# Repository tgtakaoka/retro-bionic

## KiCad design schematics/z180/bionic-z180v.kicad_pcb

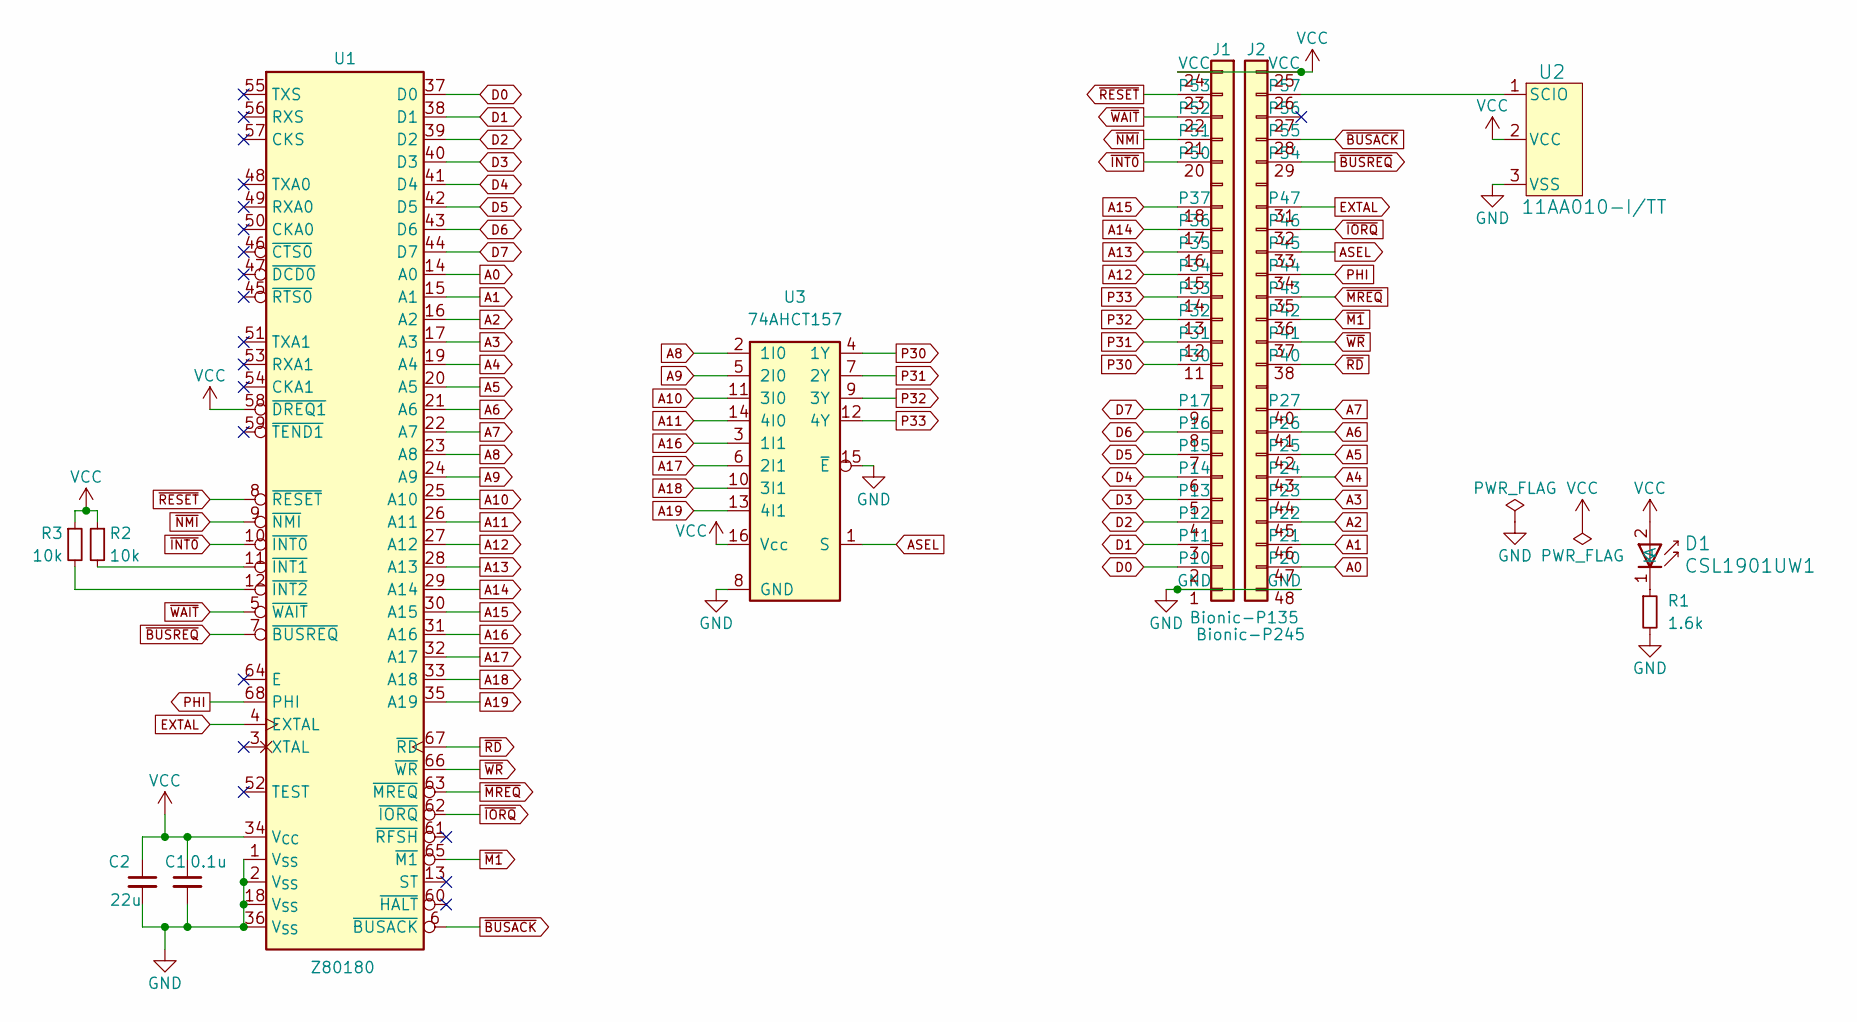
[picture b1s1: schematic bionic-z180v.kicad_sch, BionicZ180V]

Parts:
C1: 0.1u; C_0603_1608Metric_Pad1.08x0.95mm_HandSolder
C2: 22u; C_0603_1608Metric_Pad1.08x0.95mm_HandSolder
D1: CSL1901UW1; LED_CSL1901UW1_ROM-M
J1: Bionic-P135; Bionic-P135_SMT
J2: Bionic-P245; Bionic-P245_SMT
R1: 1.6k; R_0603_1608Metric_Pad0.98x0.95mm_HandSolder
R2, R3: 10k; R_0603_1608Metric_Pad0.98x0.95mm_HandSolder
U1: Z80180; 846821B1RKTP
U2: 11AA010-I/TT; SOT-23_MC_MCH-M
U3: 74AHCT157; PW16-M

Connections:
A0: J2.47 (P20), U1.14 (A0)
A1: J2.46 (P21), U1.15 (A1)
A2: J2.45 (P22), U1.16 (A2)
A3: J2.44 (P23), U1.17 (A3)
A4: J2.43 (P24), U1.19 (A4)
A5: J2.42 (P25), U1.20 (A5)
A6: J2.41 (P26), U1.21 (A6)
A7: J2.40 (P27), U1.22 (A7)
A8: U1.23 (A8), U3.2 (1I0)
A9: U1.24 (A9), U3.5 (2I0)
A10: U1.25 (A10), U3.11 (3I0)
A11: U1.26 (A11), U3.14 (4I0)
A12: J1.15 (P34), U1.27 (A12)
A13: J1.16 (P35), U1.28 (A13)
A14: J1.17 (P36), U1.29 (A14)
A15: J1.18 (P37), U1.30 (A15)
A16: U1.31 (A16), U3.3 (1I1)
A17: U1.32 (A17), U3.6 (2I1)
A18: U1.33 (A18), U3.10 (3I1)
A19: U1.35 (A19), U3.13 (4I1)
ASEL: J2.33 (P45), U3.1 (S)
D0: J1.2 (P10), U1.37 (D0)
D1: J1.3 (P11), U1.38 (D1)
D2: J1.4 (P12), U1.39 (D2)
D3: J1.5 (P13), U1.40 (D3)
D4: J1.6 (P14), U1.41 (D4)
D5: J1.7 (P15), U1.42 (D5)
D6: J1.8 (P16), U1.43 (D6)
D7: J1.9 (P17), U1.44 (D7)
EXTAL: J2.31 (P47), U1.4 (EXTAL)
GND: C1.2, C2.2, J1.1 (GND), J2.48 (GND), R1.2, U1.1 (V_{SS}), U1.2 (V_{SS}), U1.18 (V_{SS}), U1.36 (V_{SS}), U2.3 (VSS), U3.8 (GND), U3.15 (~E)
unnamed: D1.1 (K), R1.1
unnamed: J2.26 (P57), U2.1 (SCIO)
unnamed: R2.2, U1.11 (~INT1)
unnamed: R3.2, U1.12 (~INT2)
P30: J1.11 (P30), U3.4 (1Y)
P31: J1.12 (P31), U3.7 (2Y)
P32: J1.13 (P32), U3.9 (3Y)
P33: J1.14 (P33), U3.12 (4Y)
PHI: J2.34 (P44), U1.68 (PHI)
VCC: C1.1, C2.1, D1.2 (A), J1.24 (VCC), J2.25 (VCC), R2.1, R3.1, U1.34 (V_{CC}), U1.58 (~DREQ1), U2.2 (VCC), U3.16 (Vcc)
~BUSACK: J2.28 (P55), U1.6 (~BUSACK)
~BUSREQ: J2.29 (P54), U1.7 (~BUSREQ)
~INT0: J1.20 (P50), U1.10 (~INT0)
~IORQ: J2.32 (P46), U1.62 (~IORQ)
~M1: J2.36 (P42), U1.65 (~M1)
~MREQ: J2.35 (P43), U1.63 (~MREQ)
~NMI: J1.21 (P51), U1.9 (~NMI)
~RD: J2.38 (P40), U1.67 (~RD)
~RESET: J1.23 (P53), U1.8 (~RESET)
~WAIT: J1.22 (P52), U1.5 (~WAIT)
~WR: J2.37 (P41), U1.66 (~WR)

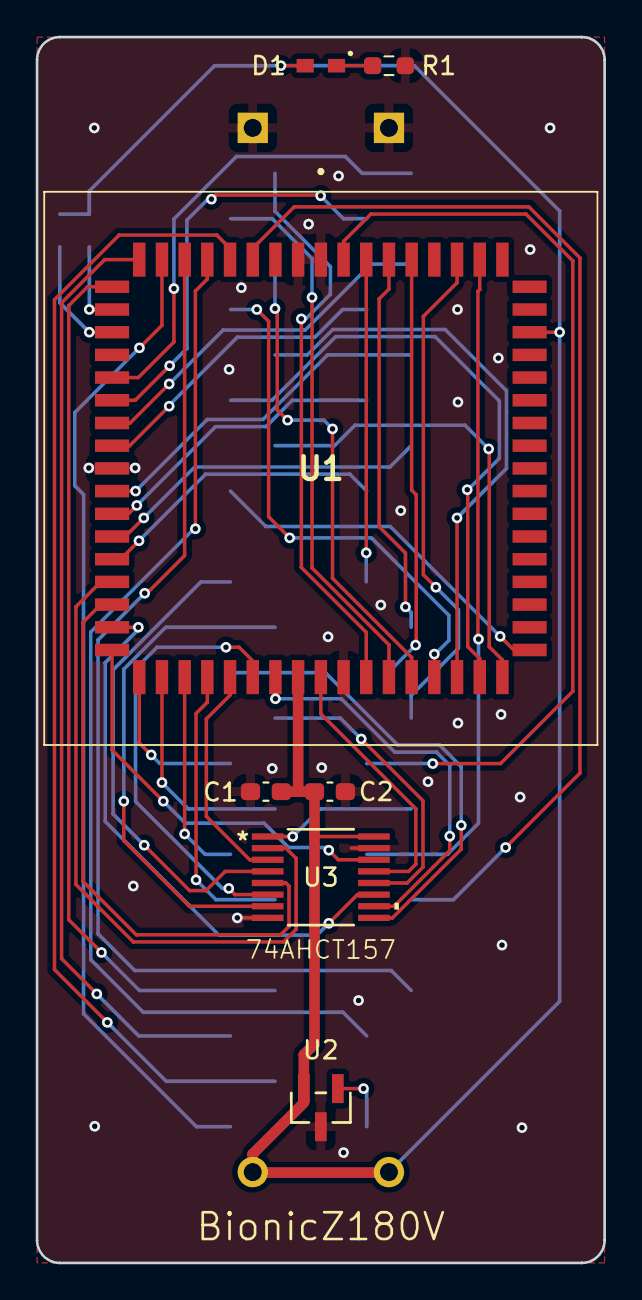
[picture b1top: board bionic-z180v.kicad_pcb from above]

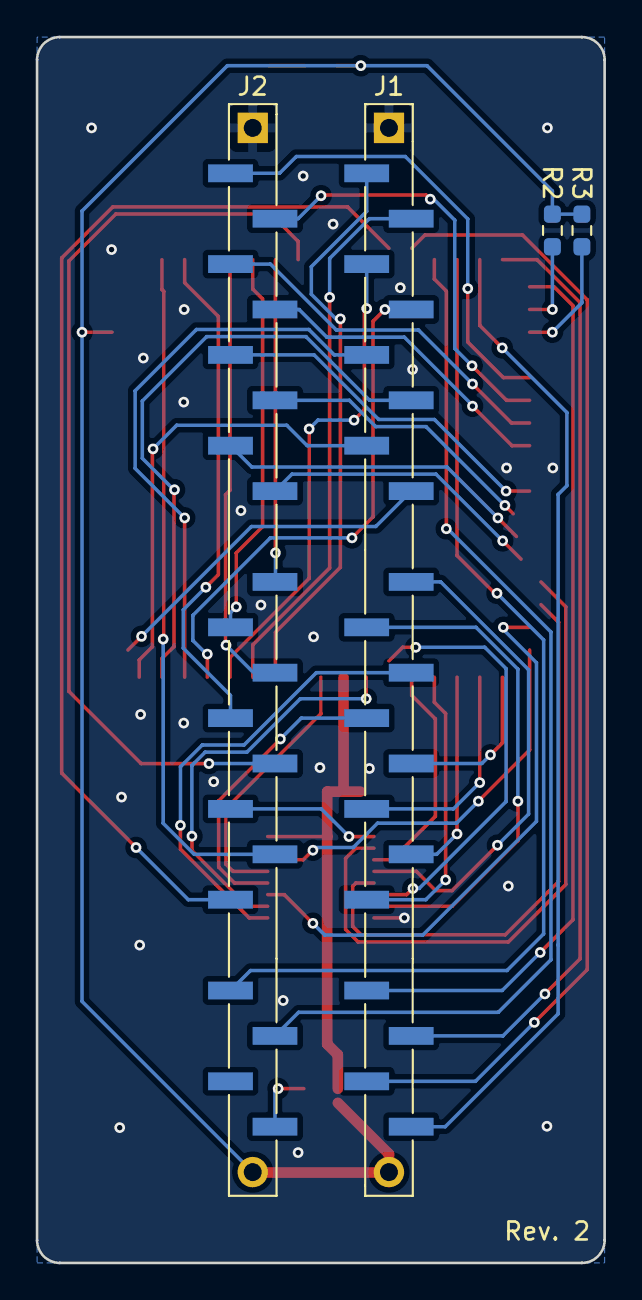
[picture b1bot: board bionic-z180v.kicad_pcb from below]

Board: 2 copper layers, 31.7 x 68.6 mm, 11 parts (4 on the bottom side), 52 nets.

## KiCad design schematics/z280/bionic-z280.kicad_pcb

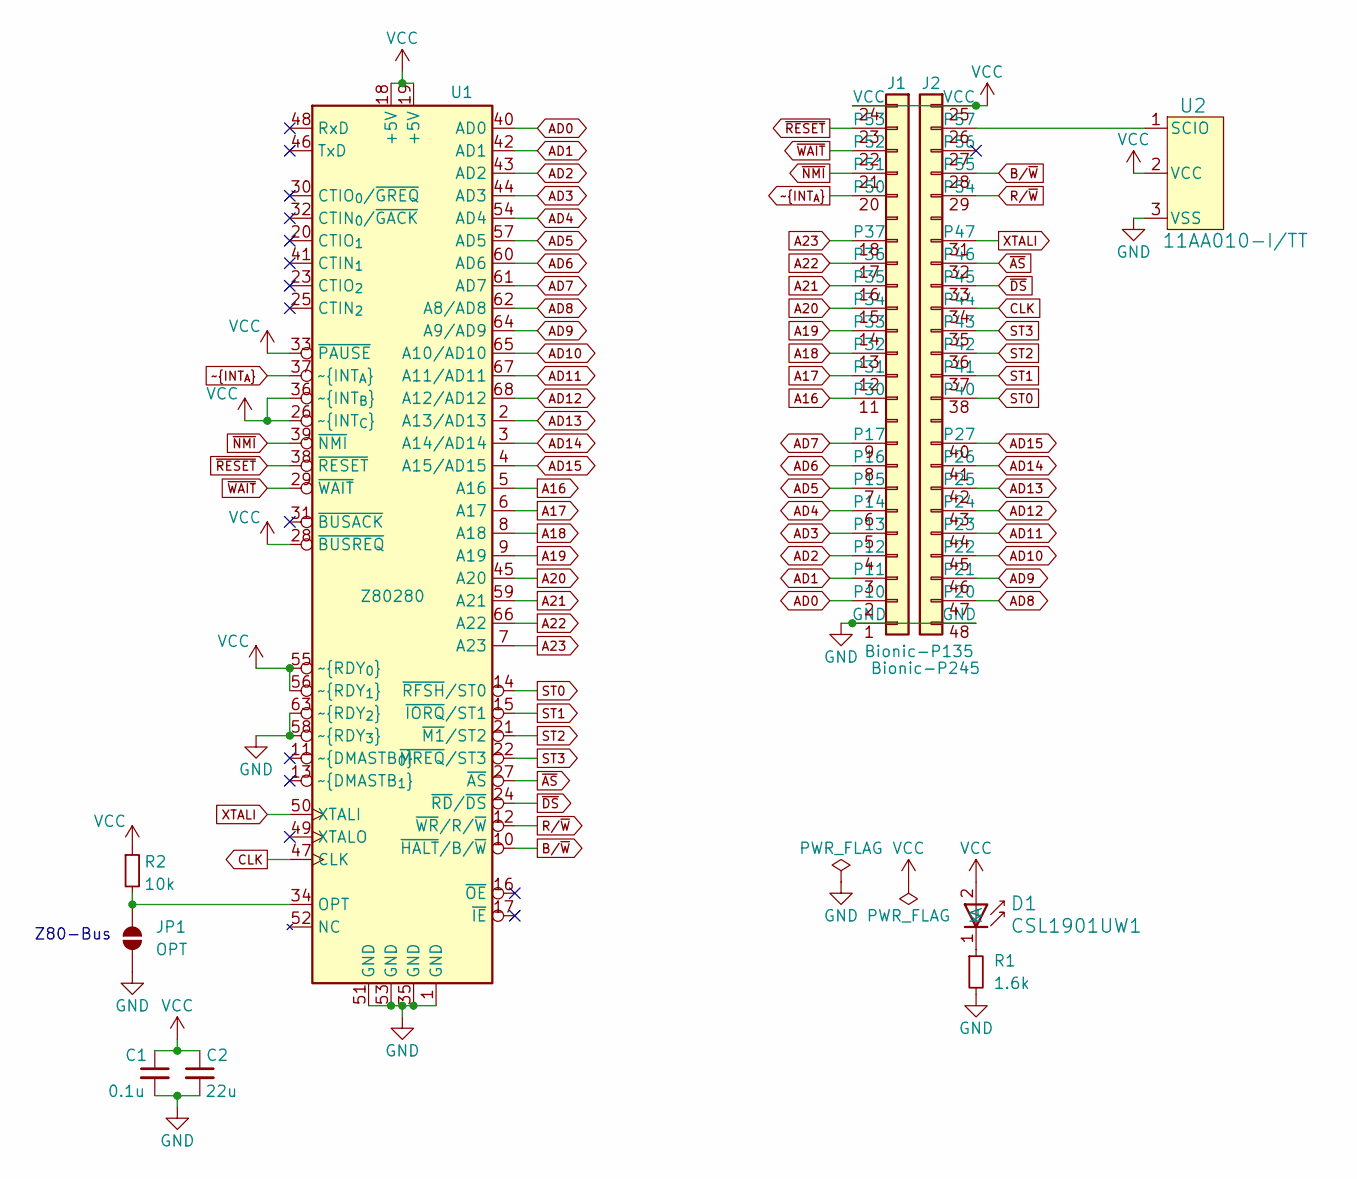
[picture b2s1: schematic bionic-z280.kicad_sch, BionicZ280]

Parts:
C1: 0.1u; C_0603_1608Metric_Pad1.08x0.95mm_HandSolder
C2: 22u; C_0603_1608Metric_Pad1.08x0.95mm_HandSolder
D1: CSL1901UW1; LED_CSL1901UW1_ROM-M
J1: Bionic-P135; Bionic-P135_SMT
J2: Bionic-P245; Bionic-P245_SMT
JP1: OPT; SolderJumper-2_P1.3mm_Open_TrianglePad1.0x1.5mm
R1: 1.6k; R_0603_1608Metric_Pad0.98x0.95mm_HandSolder
R2: 10k; R_0603_1608Metric_Pad0.98x0.95mm_HandSolder
U1: Z80280; 846821B1RKTP
U2: 11AA010-I/TT; SOT-23_MC_MCH-M

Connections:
A16: J1.11 (P30), U1.5 (A16)
A17: J1.12 (P31), U1.6 (A17)
A18: J1.13 (P32), U1.8 (A18)
A19: J1.14 (P33), U1.9 (A19)
A20: J1.15 (P34), U1.45 (A20)
A21: J1.16 (P35), U1.59 (A21)
A22: J1.17 (P36), U1.66 (A22)
A23: J1.18 (P37), U1.7 (A23)
AD0: J1.2 (P10), U1.40 (AD0)
AD1: J1.3 (P11), U1.42 (AD1)
AD2: J1.4 (P12), U1.43 (AD2)
AD3: J1.5 (P13), U1.44 (AD3)
AD4: J1.6 (P14), U1.54 (AD4)
AD5: J1.7 (P15), U1.57 (AD5)
AD6: J1.8 (P16), U1.60 (AD6)
AD7: J1.9 (P17), U1.61 (AD7)
AD8: J2.47 (P20), U1.62 (A8/AD8)
AD9: J2.46 (P21), U1.64 (A9/AD9)
AD10: J2.45 (P22), U1.65 (A10/AD10)
AD11: J2.44 (P23), U1.67 (A11/AD11)
AD12: J2.43 (P24), U1.68 (A12/AD12)
AD13: J2.42 (P25), U1.2 (A13/AD13)
AD14: J2.41 (P26), U1.3 (A14/AD14)
AD15: J2.40 (P27), U1.4 (A15/AD15)
B/~W: J2.28 (P55), U1.10 (~HALT/B/~W)
CLK: J2.34 (P44), U1.47 (CLK)
GND: C1.2, C2.2, J1.1 (GND), J2.48 (GND), JP1.1 (A), R1.2, U1.1 (GND), U1.35 (GND), U1.51 (GND), U1.53 (GND), U1.58 (~RDY_{3}), U1.63 (~RDY_{2}), U2.3 (VSS)
unnamed: D1.1 (K), R1.1
unnamed: J2.26 (P57), U2.1 (SCIO)
unnamed: JP1.2 (B), R2.2, U1.34 (OPT)
R/~W: J2.29 (P54), U1.12 (~WR/R/~W)
ST0: J2.38 (P40), U1.14 (~RFSH/ST0)
ST1: J2.37 (P41), U1.15 (~IORQ/ST1)
ST2: J2.36 (P42), U1.21 (~M1/ST2)
ST3: J2.35 (P43), U1.22 (~MREQ/ST3)
VCC: C1.1, C2.1, D1.2 (A), J1.24 (VCC), J2.25 (VCC), R2.1, U1.18 (+5V), U1.19 (+5V), U1.26 (~INT_{C}), U1.28 (~BUSREQ), U1.33 (~PAUSE), U1.36 (~INT_{B}), U1.55 (~RDY_{0}), U1.56 (~RDY_{1}), U2.2 (VCC)
XTALI: J2.31 (P47), U1.50 (XTALI)
~AS: J2.32 (P46), U1.27 (~AS)
~DS: J2.33 (P45), U1.24 (~RD/~DS)
~INT_{A}: J1.20 (P50), U1.37 (~INT_{A})
~NMI: J1.21 (P51), U1.39 (~NMI)
~RESET: J1.23 (P53), U1.38 (~RESET)
~WAIT: J1.22 (P52), U1.29 (~WAIT)

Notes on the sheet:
Z80-Bus

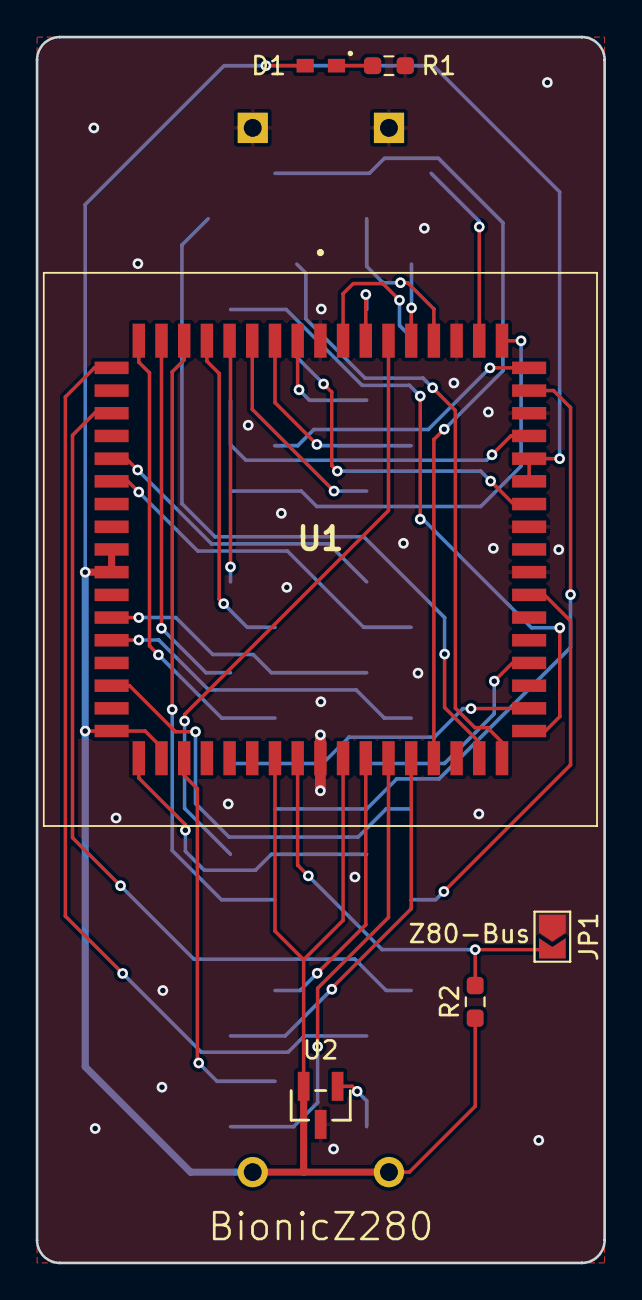
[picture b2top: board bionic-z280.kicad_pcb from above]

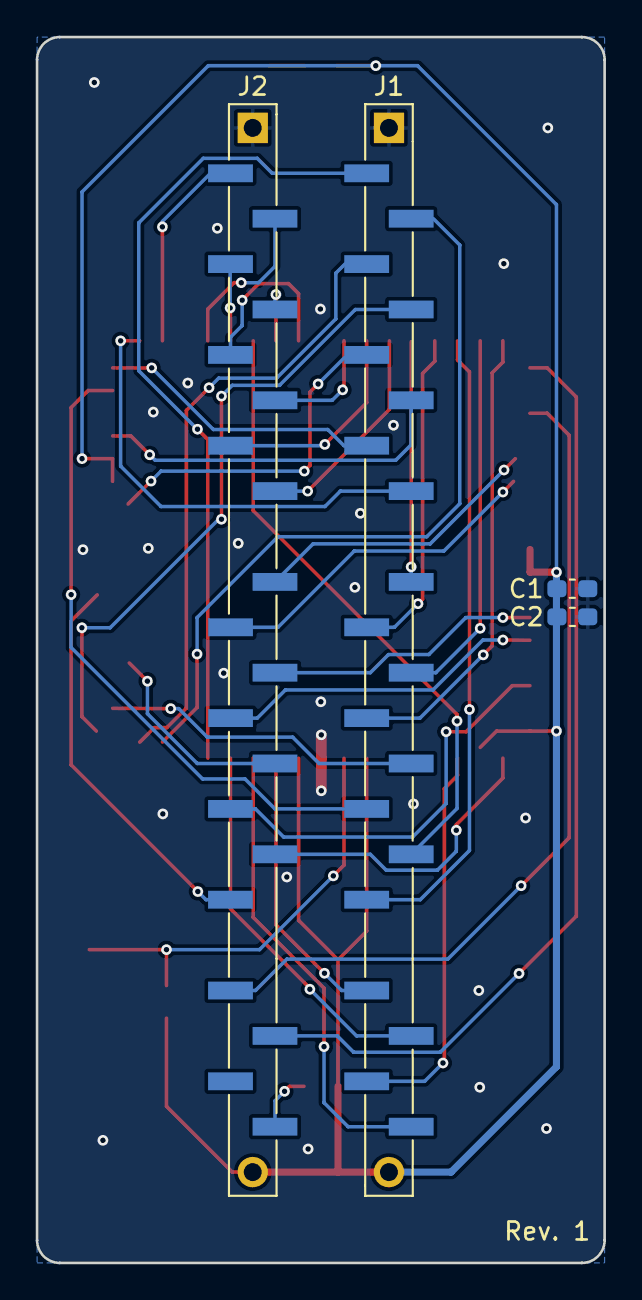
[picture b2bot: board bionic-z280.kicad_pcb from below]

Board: 2 copper layers, 31.7 x 68.6 mm, 10 parts (4 on the bottom side), 43 nets.

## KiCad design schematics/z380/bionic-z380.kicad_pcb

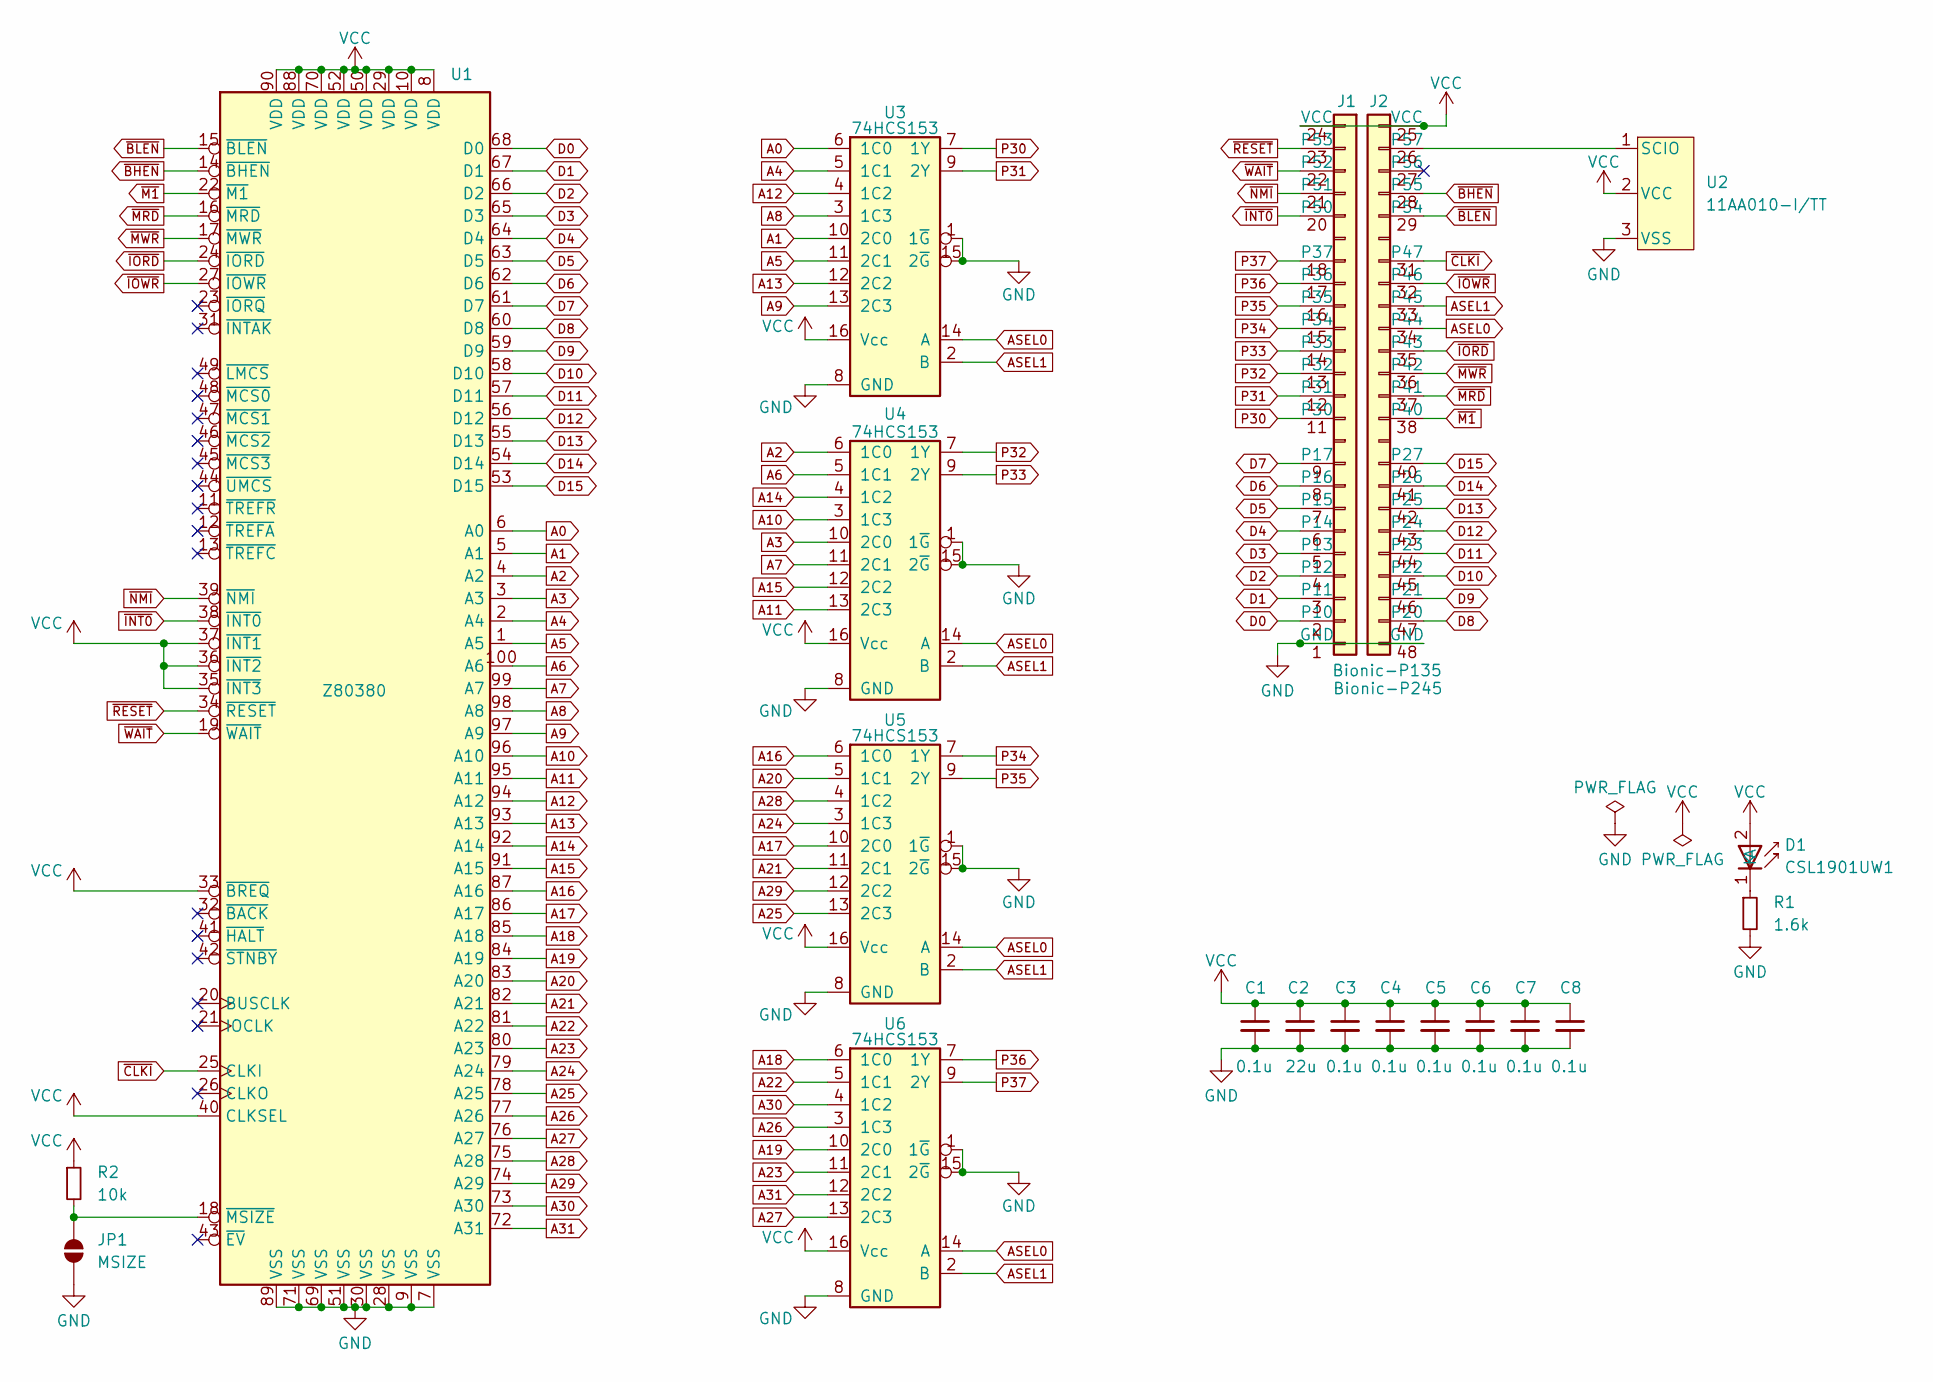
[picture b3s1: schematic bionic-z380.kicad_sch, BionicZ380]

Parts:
C1, C3, C4, C5, C6, C7, C8: 0.1u; C_0603_1608Metric_Pad1.08x0.95mm_HandSolder
C2: 22u; C_0603_1608Metric_Pad1.08x0.95mm_HandSolder
D1: CSL1901UW1; LED_CSL1901UW1_ROM-M
J1: Bionic-P135; Bionic-P135_SMT
J2: Bionic-P245; Bionic-P245_SMT
JP1: MSIZE; SolderJumper-2_P1.3mm_Open_TrianglePad1.0x1.5mm
R1: 1.6k; R_0603_1608Metric_Pad0.98x0.95mm_HandSolder
R2: 10k; R_0603_1608Metric_Pad0.98x0.95mm_HandSolder
U1: Z80380; PQFP-100_14x20mm_P0.65mm
U2: 11AA010-I/TT; SOT-23_MC_MCH-M
U3, U4, U5, U6: 74HCS153; PW16-M

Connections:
A0: U1.6 (A0), U3.6 (1C0)
A1: U1.5 (A1), U3.10 (2C0)
A2: U1.4 (A2), U4.6 (1C0)
A3: U1.3 (A3), U4.10 (2C0)
A4: U1.2 (A4), U3.5 (1C1)
A5: U1.1 (A5), U3.11 (2C1)
A6: U1.100 (A6), U4.5 (1C1)
A7: U1.99 (A7), U4.11 (2C1)
A8: U1.98 (A8), U3.3 (1C3)
A9: U1.97 (A9), U3.13 (2C3)
A10: U1.96 (A10), U4.3 (1C3)
A11: U1.95 (A11), U4.13 (2C3)
A12: U1.94 (A12), U3.4 (1C2)
A13: U1.93 (A13), U3.12 (2C2)
A14: U1.92 (A14), U4.4 (1C2)
A15: U1.91 (A15), U4.12 (2C2)
A16: U1.87 (A16), U5.6 (1C0)
A17: U1.86 (A17), U5.10 (2C0)
A18: U1.85 (A18), U6.6 (1C0)
A19: U1.84 (A19), U6.10 (2C0)
A20: U1.83 (A20), U5.5 (1C1)
A21: U1.82 (A21), U5.11 (2C1)
A22: U1.81 (A22), U6.5 (1C1)
A23: U1.80 (A23), U6.11 (2C1)
A24: U1.79 (A24), U5.3 (1C3)
A25: U1.78 (A25), U5.13 (2C3)
A26: U1.77 (A26), U6.3 (1C3)
A27: U1.76 (A27), U6.13 (2C3)
A28: U1.75 (A28), U5.4 (1C2)
A29: U1.74 (A29), U5.12 (2C2)
A30: U1.73 (A30), U6.4 (1C2)
A31: U1.72 (A31), U6.12 (2C2)
ASEL0: J2.34 (P44), U3.14 (A), U4.14 (A), U5.14 (A), U6.14 (A)
ASEL1: J2.33 (P45), U3.2 (B), U4.2 (B), U5.2 (B), U6.2 (B)
D0: J1.2 (P10), U1.68 (D0)
D1: J1.3 (P11), U1.67 (D1)
D2: J1.4 (P12), U1.66 (D2)
D3: J1.5 (P13), U1.65 (D3)
D4: J1.6 (P14), U1.64 (D4)
D5: J1.7 (P15), U1.63 (D5)
D6: J1.8 (P16), U1.62 (D6)
D7: J1.9 (P17), U1.61 (D7)
D8: J2.47 (P20), U1.60 (D8)
D9: J2.46 (P21), U1.59 (D9)
D10: J2.45 (P22), U1.58 (D10)
D11: J2.44 (P23), U1.57 (D11)
D12: J2.43 (P24), U1.56 (D12)
D13: J2.42 (P25), U1.55 (D13)
D14: J2.41 (P26), U1.54 (D14)
D15: J2.40 (P27), U1.53 (D15)
GND: C1.2, C2.2, C3.2, C4.2, C5.2, C6.2, C7.2, C8.2, J1.1 (GND), J2.48 (GND), JP1.1 (A), R1.2, U1.7 (VSS), U1.9 (VSS), U1.28 (VSS), U1.30 (VSS), U1.51 (VSS), U1.69 (VSS), U1.71 (VSS), U1.89 (VSS), U2.3 (VSS), U3.1 (1~G), U3.8 (GND), U3.15 (2~G), U4.1 (1~G), U4.8 (GND), U4.15 (2~G), U5.1 (1~G), U5.8 (GND), U5.15 (2~G), U6.1 (1~G), U6.8 (GND), U6.15 (2~G)
unnamed: D1.1 (K), R1.1
unnamed: J2.26 (P57), U2.1 (SCIO)
unnamed: JP1.2 (B), R2.2, U1.18 (~MSIZE)
P30: J1.11 (P30), U3.7 (1Y)
P31: J1.12 (P31), U3.9 (2Y)
P32: J1.13 (P32), U4.7 (1Y)
P33: J1.14 (P33), U4.9 (2Y)
P34: J1.15 (P34), U5.7 (1Y)
P35: J1.16 (P35), U5.9 (2Y)
P36: J1.17 (P36), U6.7 (1Y)
P37: J1.18 (P37), U6.9 (2Y)
VCC: C1.1, C2.1, C3.1, C4.1, C5.1, C6.1, C7.1, C8.1, D1.2 (A), J1.24 (VCC), J2.25 (VCC), R2.1, U1.8 (VDD), U1.10 (VDD), U1.29 (VDD), U1.33 (~BREQ), U1.35 (~INT3), U1.36 (~INT2), U1.37 (~INT1), U1.40 (CLKSEL), U1.50 (VDD), U1.52 (VDD), U1.70 (VDD), U1.88 (VDD), U1.90 (VDD), U2.2 (VCC), U3.16 (Vcc), U4.16 (Vcc), U5.16 (Vcc), U6.16 (Vcc)
~BHEN: J2.28 (P55), U1.14 (~BHEN)
~BLEN: J2.29 (P54), U1.15 (~BLEN)
~CLKI: J2.31 (P47), U1.25 (CLKI)
~INT0: J1.20 (P50), U1.38 (~INT0)
~IORD: J2.35 (P43), U1.24 (~IORD)
~IOWR: J2.32 (P46), U1.27 (~IOWR)
~M1: J2.38 (P40), U1.22 (~M1)
~MRD: J2.37 (P41), U1.16 (~MRD)
~MWR: J2.36 (P42), U1.17 (~MWR)
~NMI: J1.21 (P51), U1.39 (~NMI)
~RESET: J1.23 (P53), U1.34 (~RESET)
~WAIT: J1.22 (P52), U1.19 (~WAIT)

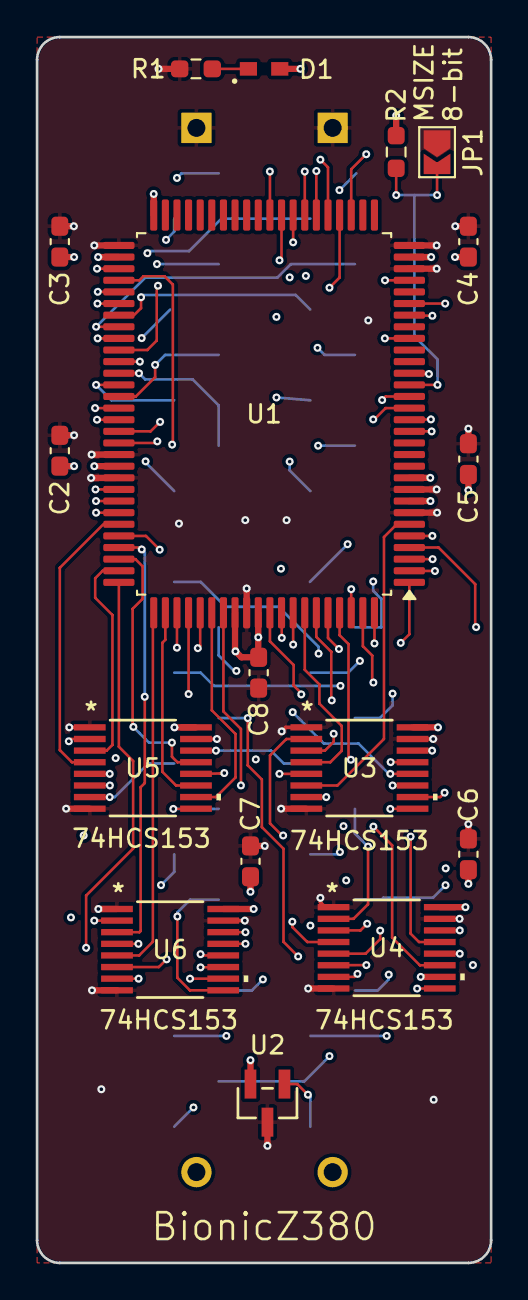
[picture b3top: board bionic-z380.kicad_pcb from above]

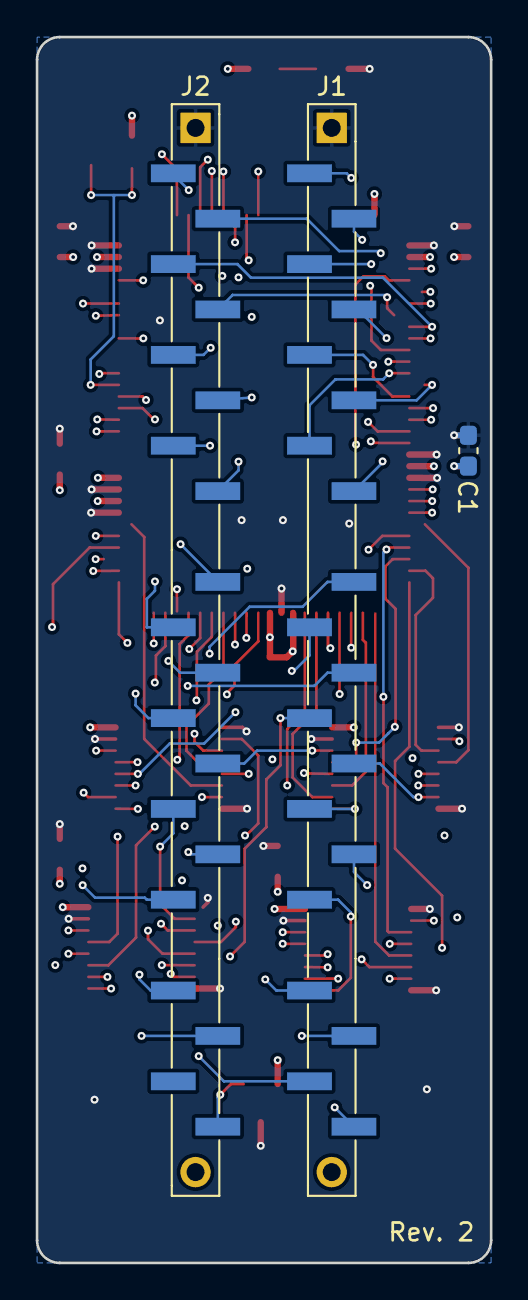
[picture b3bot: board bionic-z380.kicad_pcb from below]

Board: 4 copper layers, 25.4 x 68.6 mm, 20 parts (3 on the bottom side), 75 nets.

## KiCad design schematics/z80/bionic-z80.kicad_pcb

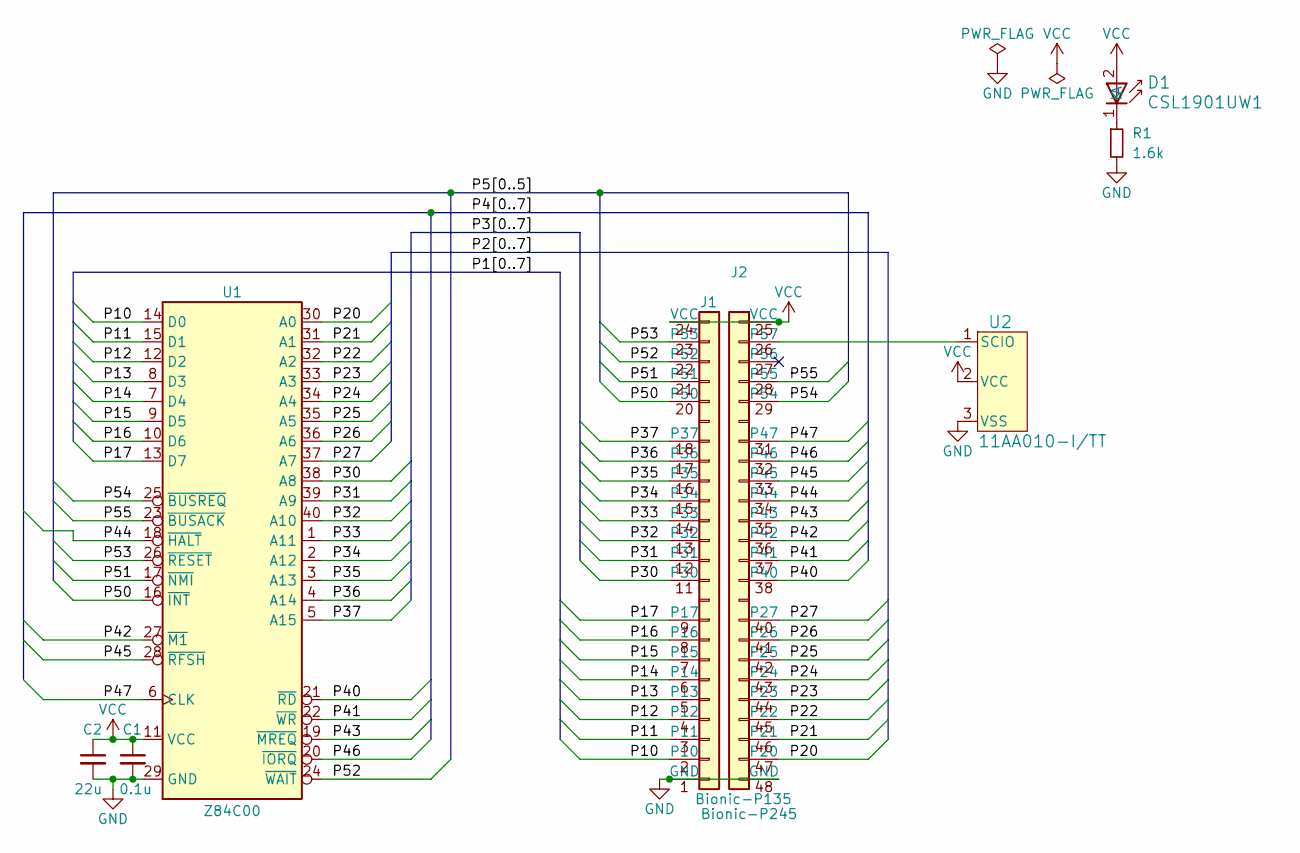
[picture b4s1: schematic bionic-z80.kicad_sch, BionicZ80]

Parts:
C1: 0.1u; C_0603_1608Metric_Pad1.08x0.95mm_HandSolder
C2: 22u; C_0603_1608Metric_Pad1.08x0.95mm_HandSolder
D1: CSL1901UW1; LED_CSL1901UW1_ROM-M
J1: Bionic-P135; Bionic-P135_THT
J2: Bionic-P245; Bionic-P245_THT
R1: 1.6k; R_0603_1608Metric_Pad0.98x0.95mm_HandSolder
U1: Z84C00; DIP-40_W15.24mm_Socket
U2: 11AA010-I/TT; SOT-23_MC_MCH-M

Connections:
/P10: J1.2 (P10), U1.14 (D0)
/P11: J1.3 (P11), U1.15 (D1)
/P12: J1.4 (P12), U1.12 (D2)
/P13: J1.5 (P13), U1.8 (D3)
/P14: J1.6 (P14), U1.7 (D4)
/P15: J1.7 (P15), U1.9 (D5)
/P16: J1.8 (P16), U1.10 (D6)
/P17: J1.9 (P17), U1.13 (D7)
/P20: J2.47 (P20), U1.30 (A0)
/P21: J2.46 (P21), U1.31 (A1)
/P22: J2.45 (P22), U1.32 (A2)
/P23: J2.44 (P23), U1.33 (A3)
/P24: J2.43 (P24), U1.34 (A4)
/P25: J2.42 (P25), U1.35 (A5)
/P26: J2.41 (P26), U1.36 (A6)
/P27: J2.40 (P27), U1.37 (A7)
/P30: J1.11 (P30), U1.38 (A8)
/P31: J1.12 (P31), U1.39 (A9)
/P32: J1.13 (P32), U1.40 (A10)
/P33: J1.14 (P33), U1.1 (A11)
/P34: J1.15 (P34), U1.2 (A12)
/P35: J1.16 (P35), U1.3 (A13)
/P36: J1.17 (P36), U1.4 (A14)
/P37: J1.18 (P37), U1.5 (A15)
/P40: J2.38 (P40), U1.21 (~RD)
/P41: J2.37 (P41), U1.22 (~WR)
/P42: J2.36 (P42), U1.27 (~M1)
/P43: J2.35 (P43), U1.19 (~MREQ)
/P44: J2.34 (P44), U1.18 (~HALT)
/P45: J2.33 (P45), U1.28 (~RFSH)
/P46: J2.32 (P46), U1.20 (~IORQ)
/P47: J2.31 (P47), U1.6 (CLK)
/P50: J1.20 (P50), U1.16 (~INT)
/P51: J1.21 (P51), U1.17 (~NMI)
/P52: J1.22 (P52), U1.24 (~WAIT)
/P53: J1.23 (P53), U1.26 (~RESET)
/P54: J2.29 (P54), U1.25 (~BUSREQ)
/P55: J2.28 (P55), U1.23 (~BUSACK)
GND: C1.2, C2.2, J1.1 (GND), J2.48 (GND), R1.2, U1.29 (GND), U2.3 (VSS)
unnamed: D1.1 (K), R1.1
unnamed: J2.26 (P57), U2.1 (SCIO)
VCC: C1.1, C2.1, D1.2 (A), J1.24 (VCC), J2.25 (VCC), U1.11 (VCC), U2.2 (VCC)

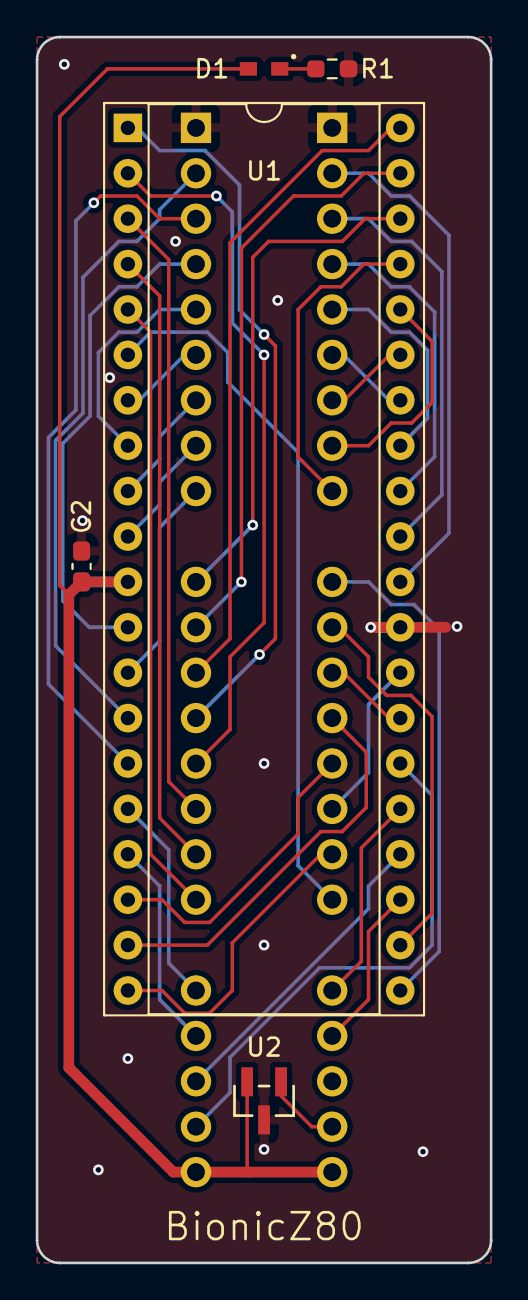
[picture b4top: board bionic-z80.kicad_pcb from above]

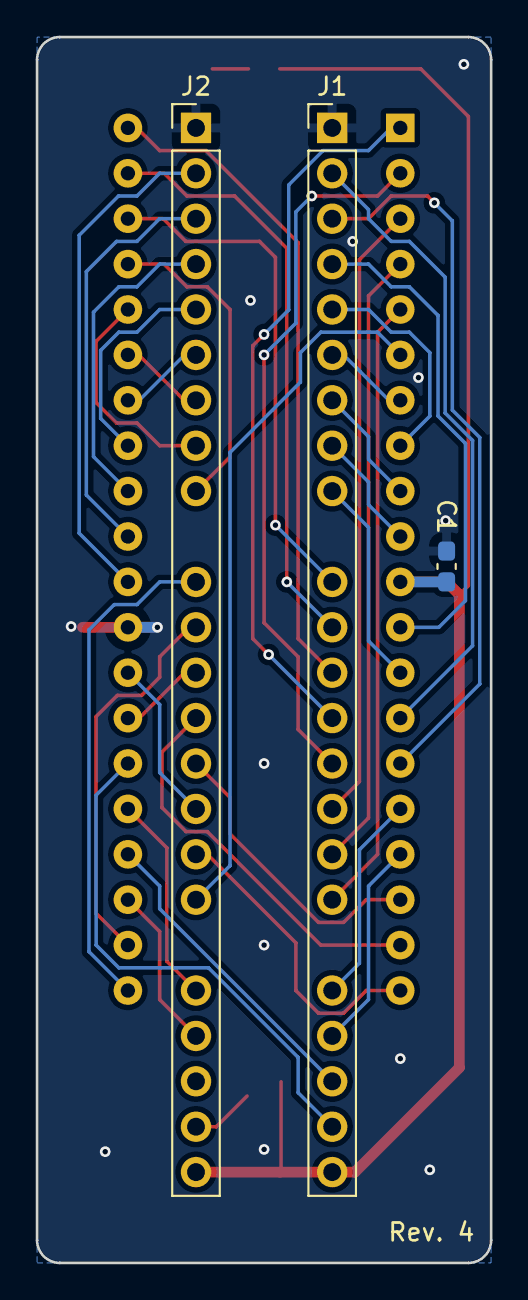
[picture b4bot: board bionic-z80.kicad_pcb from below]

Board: 2 copper layers, 25.4 x 68.6 mm, 8 parts (3 on the bottom side), 42 nets.

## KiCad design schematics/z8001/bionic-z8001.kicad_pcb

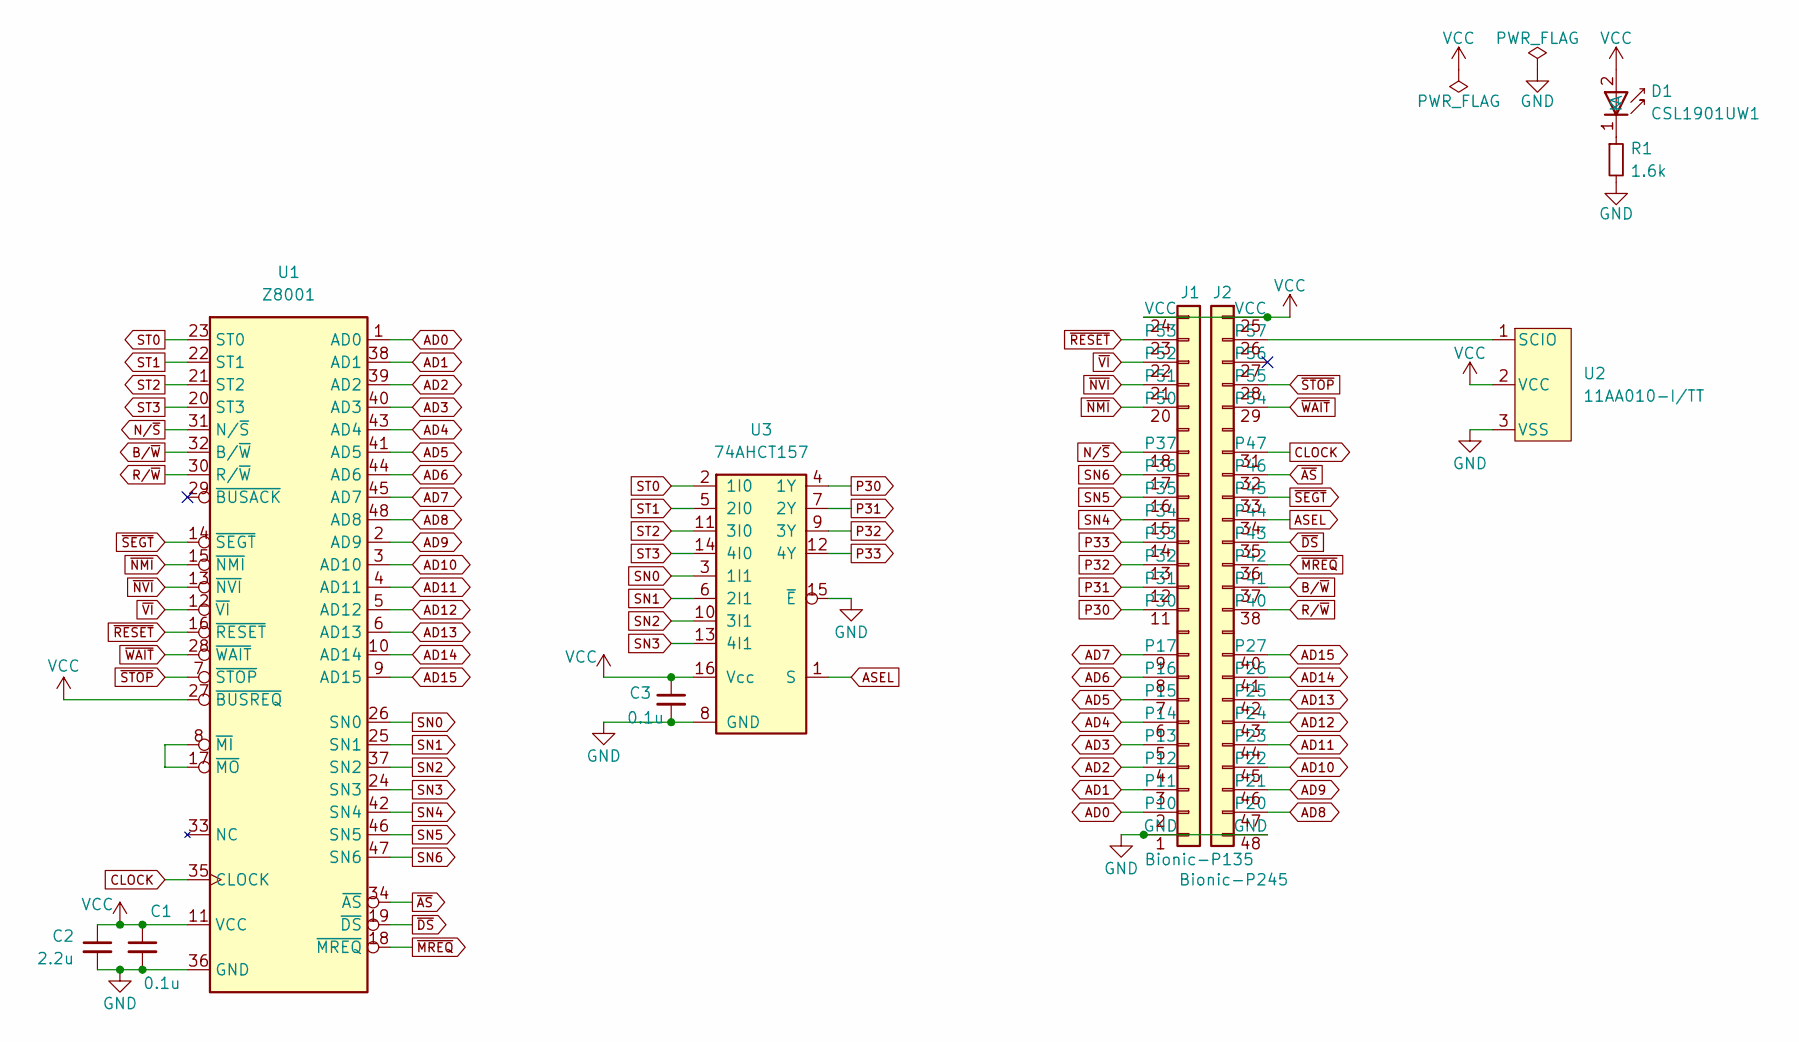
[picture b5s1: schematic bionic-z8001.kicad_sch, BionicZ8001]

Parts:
C1, C3: 0.1u; C_0603_1608Metric_Pad1.08x0.95mm_HandSolder
C2: 2.2u; C_0603_1608Metric_Pad1.08x0.95mm_HandSolder
D1: CSL1901UW1; LED_CSL1901UW1_ROM-M
J1: Bionic-P135; Bionic-P135_SMT
J2: Bionic-P245; Bionic-P245_SMT
R1: 1.6k; R_0603_1608Metric_Pad0.98x0.95mm_HandSolder
U1: Z8001; DIP-48_W15.24mm_Socket
U2: 11AA010-I/TT; SOT-23_MC_MCH-M
U3: 74AHCT157; PW16-M

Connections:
AD0: J1.2 (P10), U1.1 (AD0)
AD1: J1.3 (P11), U1.38 (AD1)
AD2: J1.4 (P12), U1.39 (AD2)
AD3: J1.5 (P13), U1.40 (AD3)
AD4: J1.6 (P14), U1.43 (AD4)
AD5: J1.7 (P15), U1.41 (AD5)
AD6: J1.8 (P16), U1.44 (AD6)
AD7: J1.9 (P17), U1.45 (AD7)
AD8: J2.47 (P20), U1.48 (AD8)
AD9: J2.46 (P21), U1.2 (AD9)
AD10: J2.45 (P22), U1.3 (AD10)
AD11: J2.44 (P23), U1.4 (AD11)
AD12: J2.43 (P24), U1.5 (AD12)
AD13: J2.42 (P25), U1.6 (AD13)
AD14: J2.41 (P26), U1.10 (AD14)
AD15: J2.40 (P27), U1.9 (AD15)
ASEL: J2.34 (P44), U3.1 (S)
B/~W: J2.37 (P41), U1.32 (B/~W)
CLOCK: J2.31 (P47), U1.35 (CLOCK)
GND: C1.2, C2.2, C3.2, J1.1 (GND), J2.48 (GND), R1.2, U1.36 (GND), U2.3 (VSS), U3.8 (GND), U3.15 (~E)
unnamed: D1.1 (K), R1.1
unnamed: J2.26 (P57), U2.1 (SCIO)
unnamed: U1.8 (~MI), U1.17 (~MO)
N/~S: J1.18 (P37), U1.31 (N/~S)
P30: J1.11 (P30), U3.4 (1Y)
P31: J1.12 (P31), U3.7 (2Y)
P32: J1.13 (P32), U3.9 (3Y)
P33: J1.14 (P33), U3.12 (4Y)
R/~W: J2.38 (P40), U1.30 (R/~W)
SN0: U1.26 (SN0), U3.3 (1I1)
SN1: U1.25 (SN1), U3.6 (2I1)
SN2: U1.37 (SN2), U3.10 (3I1)
SN3: U1.24 (SN3), U3.13 (4I1)
SN4: J1.15 (P34), U1.42 (SN4)
SN5: J1.16 (P35), U1.46 (SN5)
SN6: J1.17 (P36), U1.47 (SN6)
ST0: U1.23 (ST0), U3.2 (1I0)
ST1: U1.22 (ST1), U3.5 (2I0)
ST2: U1.21 (ST2), U3.11 (3I0)
ST3: U1.20 (ST3), U3.14 (4I0)
VCC: C1.1, C2.1, C3.1, D1.2 (A), J1.24 (VCC), J2.25 (VCC), U1.11 (VCC), U1.27 (~BUSREQ), U2.2 (VCC), U3.16 (Vcc)
~AS: J2.32 (P46), U1.34 (~AS)
~DS: J2.35 (P43), U1.19 (~DS)
~MREQ: J2.36 (P42), U1.18 (~MREQ)
~NMI: J1.20 (P50), U1.15 (~NMI)
~NVI: J1.21 (P51), U1.13 (~NVI)
~RESET: J1.23 (P53), U1.16 (~RESET)
~SEGT: J2.33 (P45), U1.14 (~SEGT)
~STOP: J2.28 (P55), U1.7 (~STOP)
~VI: J1.22 (P52), U1.12 (~VI)
~WAIT: J2.29 (P54), U1.28 (~WAIT)
